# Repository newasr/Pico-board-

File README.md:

# Pico Board Replica

## Overview
This project is a replica of the Raspberry Pi Pico board, designed from scratch as a learning and practice exercise.

## Features
- Based on the RP2040 microcontroller
- Same form factor and pinout as the original Raspberry Pi Pico
- Designed using Kicad
- Fully open-source hardware

## Design Files
- **Schematics:**  
  
- **Final Product (3D View):**  
  
- **BOM (Bill of Materials):** [Link to BOM](https://github.com/newasr/Pico-board-/tree/main/bom)
- **3D View:** [Link](https://github.com/newasr/Pico-board-/blob/main/assets/my-template.stl)

## Contributing
Feel free to open issues or submit pull requests to improve this project.

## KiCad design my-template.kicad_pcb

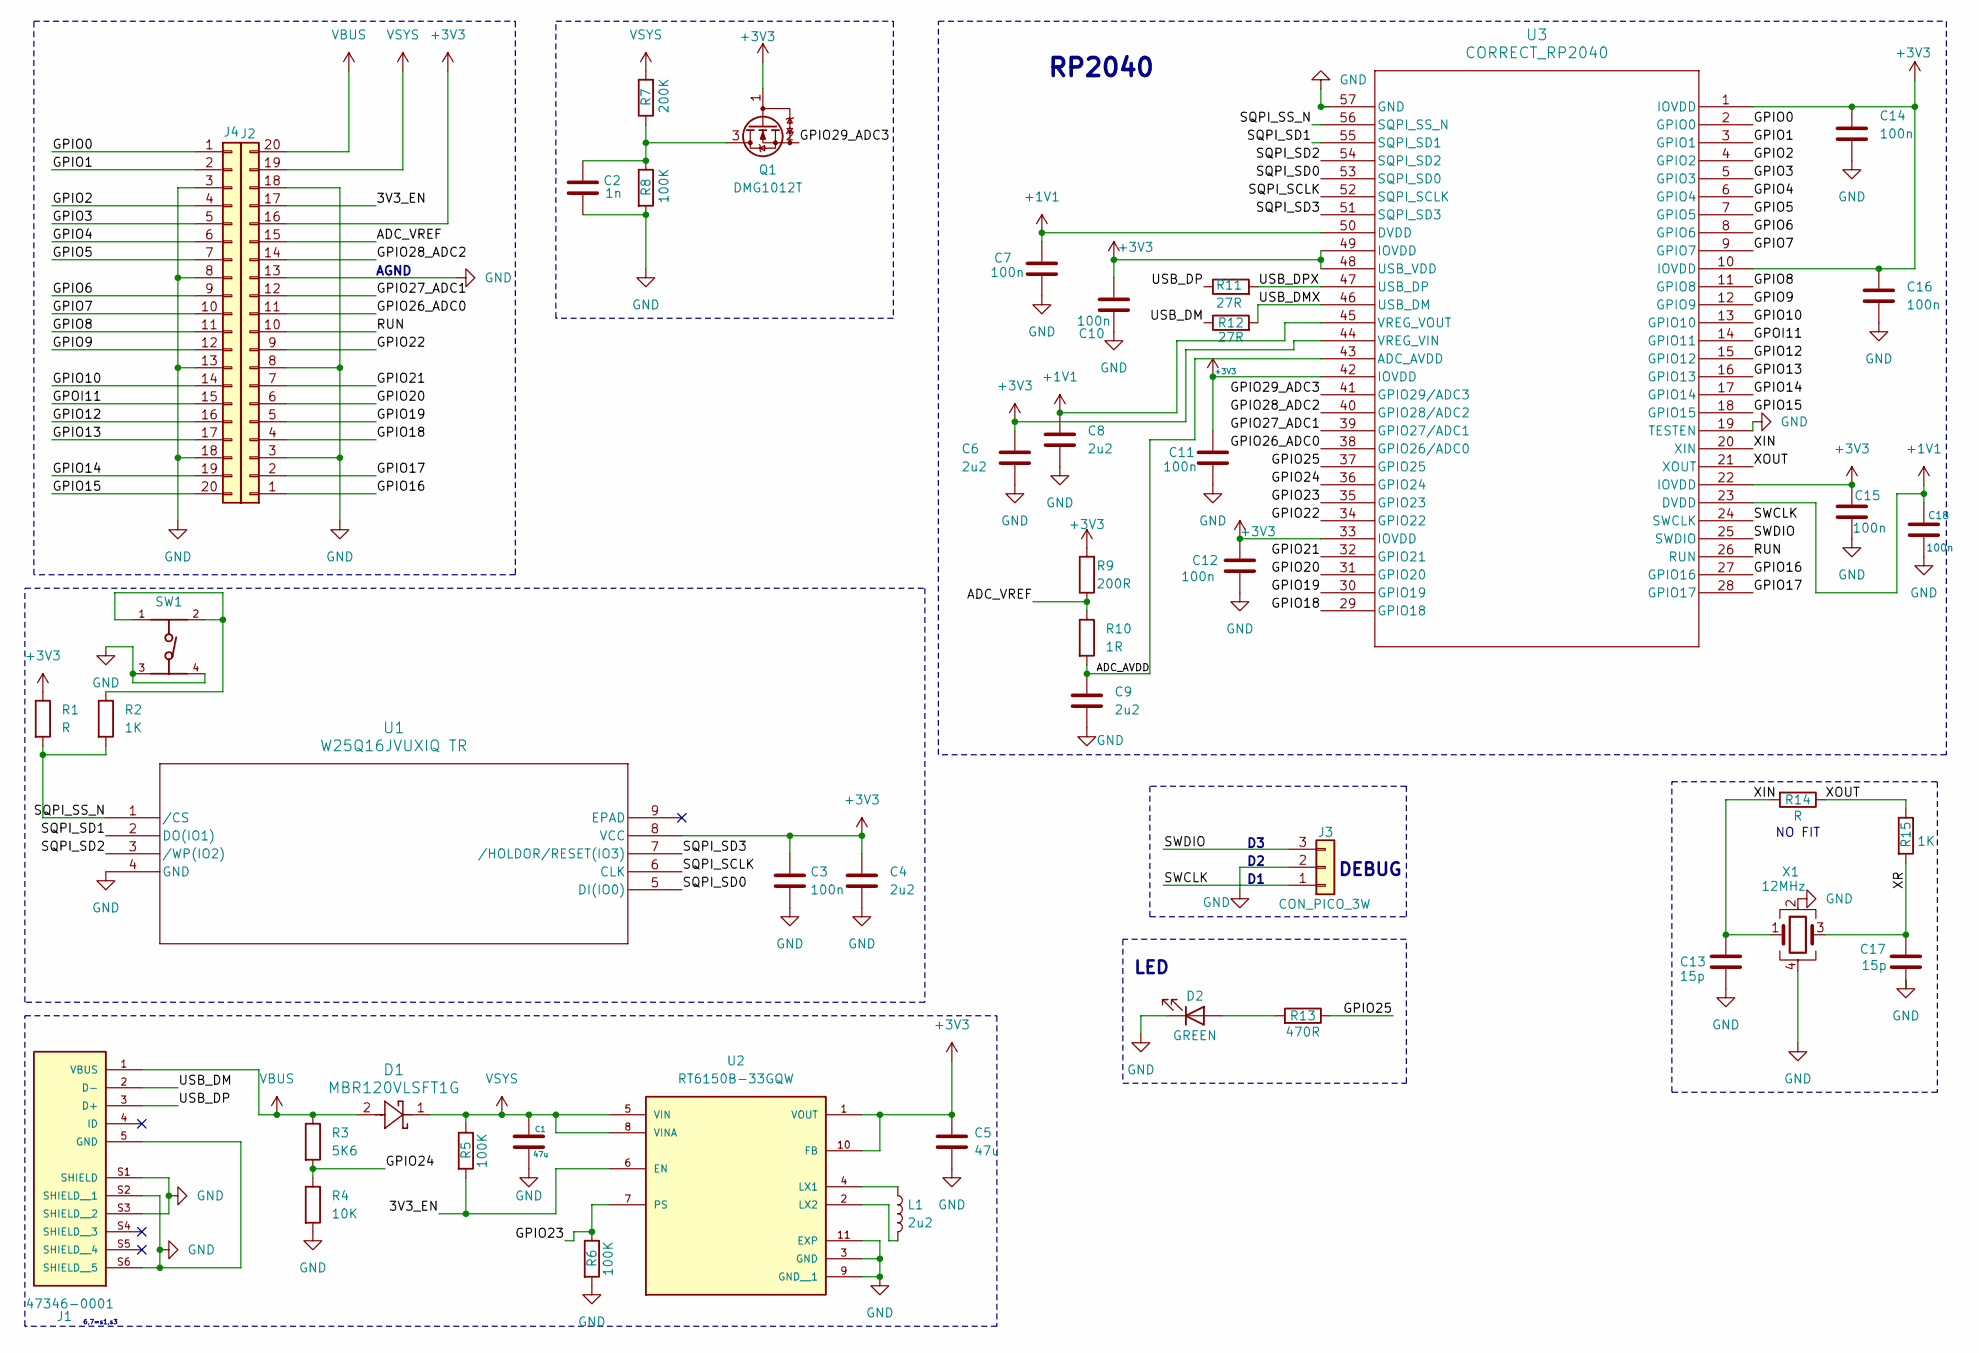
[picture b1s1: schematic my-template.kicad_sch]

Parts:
C1, C5: 47u; C_0805_2012Metric; Digikey Part# TACR476M006XTA
C2: 1n; C_0201_0603Metric; Digikey Part# GRM033R71E102KA01D
C3, C7, C10, C11, C12, C14, C15, C16, C18: 100n; C_0201_0603Metric; Digikey Part# 0201W104K100LE
C4, C6, C8, C9: 2u2; C_0402_1005Metric; Digikey Part# 0402W225K100HI
C13, C17: 15p; C_0201_0603Metric; Digikey Part# GRM0335C1E150JA01D
D1: MBR120VLSFT1G; Digikey Part# MBR120VLSFT1G
D2: GREEN; LED_0402_1005Metric; Digikey Part# 150040GS73240
J1: 47346-0001; MOLEX_47346-0001; PARTREV E; Digikey Part# 0473460001
J2: Conn_01x20; part_2_40_pin
J3: CON_PICO_3W; 3_pin_connector
J4: Conn_01x20; part_1_40_pin
L1: 2u2; L_0402_1005Metric; Digikey Part# MLZ1005M2R2WT000
Q1: DMG1012T; SOT-523
R1, R14: R; R_0402_1005Metric
R2, R15: 1K; R_0402_1005Metric; Digikey Part# RC0402JR-071KL
R3: 5K6; R_0402_1005Metric; Digikey Part# RC0402FR-075K6L
R4: 10K; R_0402_1005Metric; Digikey Part# RC1005F103CS
R5, R6, R8: 100K; R_0402_1005Metric; Digikey Part# RC0402FR-07100KL
R7: 200K; R_0402_1005Metric; Digikey Part# RC0402JR-103K3L
R9: 200R; R_0603_1608Metric; Digikey Part# ERJ-2RKF2000X
R10: 1R; R_0402_1005Metric; Digikey Part# CRGCQ0402J1R0
R11, R12: 27R; R_0402_1005Metric; Digikey Part# CPF0402B27RE1
R13: 470R; R_0402_1005Metric; Digikey Part# CRG0402J470R
SW1: 434133025816; PART-NUMBER 434133025816; Digikey Part# 434133025816
U1: W25Q16JVUXIQ TR; W25Q16JVUXIQ; Digikey Part# W25Q16JVUXIQ TR
U2: RT6150B-33GQW; PARTREV July 2018; Digikey Part# RT6150B-33GQW
U3: CORRECT_RP2040; Digikey Part# SC0914(7)
X1: 12MHz; Oscillator_SMD_SeikoEpson_SG210-4Pin_2.5x2.0mm; Digikey Part# ECS-2520MVLC-120-CN-TR

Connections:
+1V1: C7.1, C8.1, C18.1, U3.23 (DVDD), U3.45 (VREG_VOUT), U3.50 (DVDD)
+3V3: C3.1, C4.1, C5.1, C6.1, C10.1, C11.1, C12.1, C14.1, C15.1, C16.1, J2.16, Q1.1 (G), R1.1, R9.2, U1.8 (VCC), U2.1 (VOUT), U2.10 (FB), U3.1 (IOVDD), U3.10 (IOVDD), U3.22 (IOVDD), U3.33 (IOVDD), U3.42 (IOVDD), U3.44 (VREG_VIN), U3.48 (USB_VDD), U3.49 (IOVDD)
/3V3_EN: J2.17, R5.2, U2.6 (EN)
/ADC_AVDD: C9.1, R10.2, U3.43 (ADC_AVDD)
/ADC_VREF: J2.15, R9.1, R10.1
/GPIO0: J4.1, U3.2 (GPIO0)
/GPIO1: J4.2, U3.3 (GPIO1)
/GPIO2: J4.4, U3.4 (GPIO2)
/GPIO3: J4.5, U3.5 (GPIO3)
/GPIO4: J4.6, U3.6 (GPIO4)
/GPIO5: J4.7, U3.7 (GPIO5)
/GPIO6: J4.9, U3.8 (GPIO6)
/GPIO7: J4.10, U3.9 (GPIO7)
/GPIO8: J4.11, U3.11 (GPIO8)
/GPIO9: J4.12, U3.12 (GPIO9)
/GPIO10: J4.14, U3.13 (GPIO10)
/GPIO12: J4.16, U3.15 (GPIO12)
/GPIO13: J4.17, U3.16 (GPIO13)
/GPIO14: J4.19, U3.17 (GPIO14)
/GPIO15: J4.20, U3.18 (GPIO15)
/GPIO16: J2.1, U3.27 (GPIO16)
/GPIO17: J2.2, U3.28 (GPIO17)
/GPIO18: J2.4, U3.29 (GPIO18)
/GPIO19: J2.5, U3.30 (GPIO19)
/GPIO20: J2.6, U3.31 (GPIO20)
/GPIO21: J2.7, U3.32 (GPIO21)
/GPIO22: J2.9, U3.34 (GPIO22)
/GPIO23: R6.1, U2.7 (PS), U3.35 (GPIO23)
/GPIO24: R3.2, R4.1, U3.36 (GPIO24)
/GPIO25: R13.1, U3.37 (GPIO25)
/GPIO26_ADC0: J2.11, U3.38 (GPIO26/ADC0)
/GPIO27_ADC1: J2.12, U3.39 (GPIO27/ADC1)
/GPIO28_ADC2: J2.14, U3.40 (GPIO28/ADC2)
/GPIO29_ADC3: Q1.2 (S), U3.41 (GPIO29/ADC3)
/GPOI11: J4.15, U3.14 (GPIO11)
/RUN: J2.10, U3.26 (RUN)
/SQPI_SCLK: U1.6 (CLK), U3.52 (SQPI_SCLK)
/SQPI_SD0: U1.5 (DI(IO0)), U3.53 (SQPI_SD0)
/SQPI_SD1: U1.2 (DO(IO1)), U3.55 (SQPI_SD1)
/SQPI_SD2: U1.3 (/WP(IO2)), U3.54 (SQPI_SD2)
/SQPI_SD3: U1.7 (/HOLDOR/RESET(IO3)), U3.51 (SQPI_SD3)
/SQPI_SS_N: R1.2, R2.2, U1.1 (/CS), U3.56 (SQPI_SS_N)
/SWCLK: J3.1, U3.24 (SWCLK)
/SWDIO: J3.3, U3.25 (SWDIO)
/USB_DM: J1.2 (D-), R12.1
/USB_DMX: R12.2, U3.46 (USB_DM)
/USB_DP: J1.3 (D+), R11.1
/USB_DPX: R11.2, U3.47 (USB_DP)
/XIN: C13.1, R14.2, U3.20 (XIN), X1.1
/XOUT: R14.1, R15.1, U3.21 (XOUT)
/XR: C17.1, R15.2, X1.3
GND: C1.2, C2.2, C3.2, C4.2, C5.2, C6.2, C7.2, C8.2, C9.2, C10.2, C11.2, C12.2, C13.2, C14.2, C15.2, C16.2, C17.2, C18.2, D2.1 (K), J1.5 (GND), J1.S1 (SHIELD), J1.S2 (SHIELD__1), J1.S3 (SHIELD__2), J1.S6 (SHIELD__5), J2.3, J2.8, J2.13, J2.18, J3.2, J4.3, J4.8, J4.13, J4.18, R4.2, R6.2, R8.2, SW1.3, SW1.4, U1.4 (GND), U2.3 (GND), U2.9 (GND__1), U2.11 (EXP), U3.19 (TESTEN), U3.57 (GND), X1.2, X1.4
unnamed: D2.2 (A), R13.2
unnamed: C2.1, Q1.3 (D), R7.1, R8.1
unnamed: R2.1, SW1.1, SW1.2
unnamed: L1.1, U2.4 (LX1)
unnamed: L1.2, U2.2 (LX2)
VBUS: D1.2, J1.1 (VBUS), J2.20, R3.1
VSYS: C1.1, D1.1, J2.19, R5.1, R7.2, U2.5 (VIN), U2.8 (VINA)

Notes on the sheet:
DEBUG
NO FIT
AGND
6,7=s1,s3
RP2040
LED

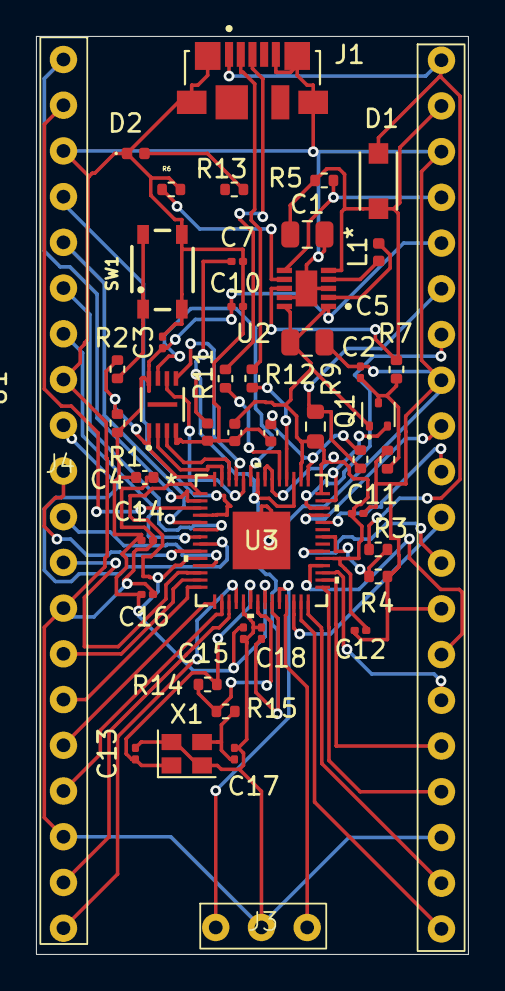
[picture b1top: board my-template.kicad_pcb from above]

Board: 2 copper layers, 24.0 x 51.0 mm, 46 parts (0 on the bottom side), 59 nets.

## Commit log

2025-02-02 added 3d files
2025-02-02 gerber go brrr
2025-02-02 added remaining files
2025-02-03 added assets
    circuit, final prodcut, 3d view step file
